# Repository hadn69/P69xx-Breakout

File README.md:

A breakout for Tektronixs P69xx cables, designed for P6960 cables but should work with the others.

It **should** work right now but i would like to make the layout a bit cleaner and get the first small batch made.

### Previous version renders complete with spelling mistakes!

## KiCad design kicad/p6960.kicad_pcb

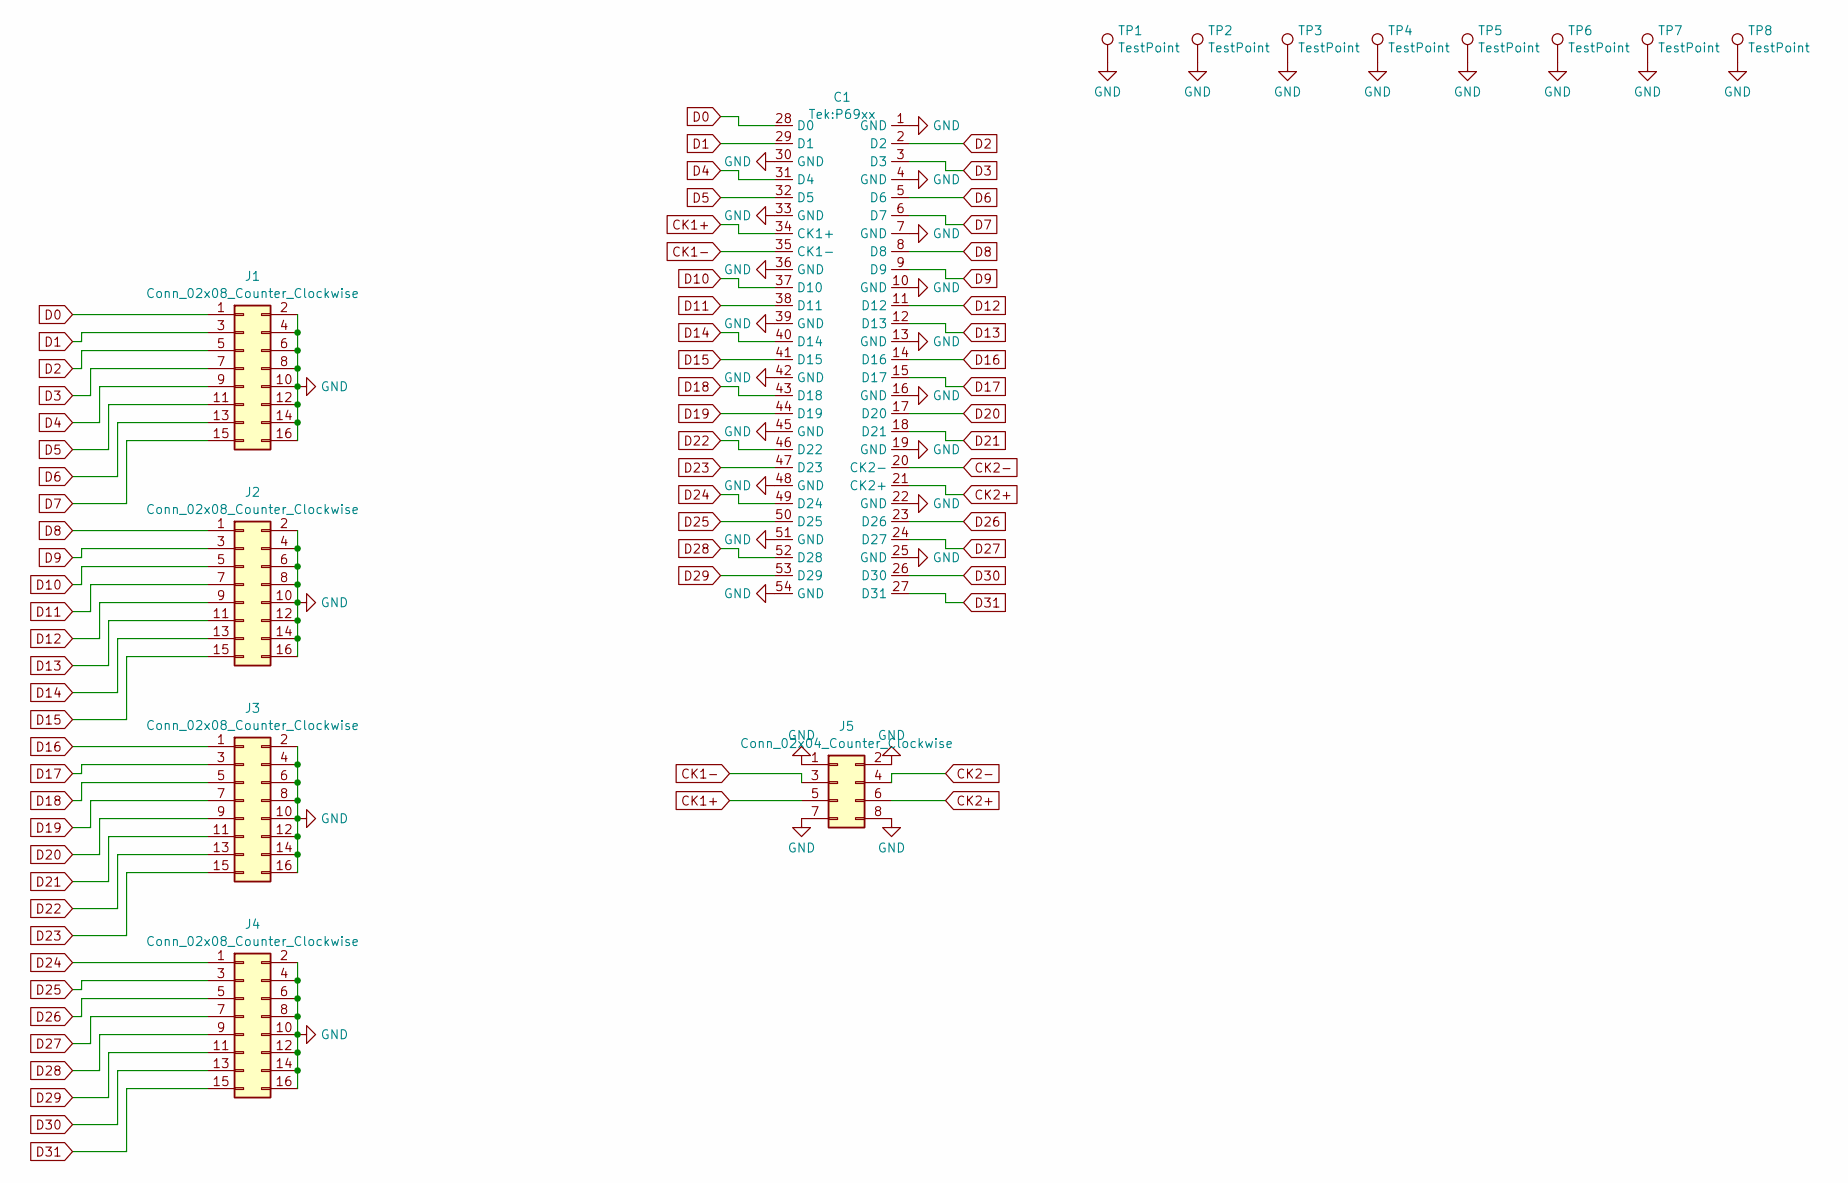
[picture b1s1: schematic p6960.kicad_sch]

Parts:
C1: P69xx
J1, J2, J3, J4: Conn_02x08_Counter_Clockwise; PinHeader_2x08_P2.54mm_Vertical
J5: Conn_02x04_Counter_Clockwise; PinHeader_2x04_P2.54mm_Horizontal
TP1, TP2, TP3, TP4, TP5, TP6, TP7, TP8: TestPoint; TestPoint_Pad_2.0x2.0mm

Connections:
CK1+: C1.34 (CK1+), J5.5
CK1-: C1.35 (CK1-), J5.3
CK2+: C1.21 (CK2+), J5.6
CK2-: C1.20 (CK2-), J5.4
D0: C1.28 (D0), J1.1
D1: C1.29 (D1), J1.3
D2: C1.2 (D2), J1.5
D3: C1.3 (D3), J1.7
D4: C1.31 (D4), J1.9
D5: C1.32 (D5), J1.11
D6: C1.5 (D6), J1.13
D7: C1.6 (D7), J1.15
D8: C1.8 (D8), J2.1
D9: C1.9 (D9), J2.3
D10: C1.37 (D10), J2.5
D11: C1.38 (D11), J2.7
D12: C1.11 (D12), J2.9
D13: C1.12 (D13), J2.11
D14: C1.40 (D14), J2.13
D15: C1.41 (D15), J2.15
D16: C1.14 (D16), J3.1
D17: C1.15 (D17), J3.3
D18: C1.43 (D18), J3.5
D19: C1.44 (D19), J3.7
D20: C1.17 (D20), J3.9
D21: C1.18 (D21), J3.11
D22: C1.46 (D22), J3.13
D23: C1.47 (D23), J3.15
D24: C1.49 (D24), J4.1
D25: C1.50 (D25), J4.3
D26: C1.23 (D26), J4.5
D27: C1.24 (D27), J4.7
D28: C1.52 (D28), J4.9
D29: C1.53 (D29), J4.11
D30: C1.26 (D30), J4.13
D31: C1.27 (D31), J4.15
GND: C1.1 (GND), C1.4 (GND), C1.7 (GND), C1.10 (GND), C1.13 (GND), C1.16 (GND), C1.19 (GND), C1.22 (GND), C1.25 (GND), C1.30 (GND), C1.33 (GND), C1.36 (GND), C1.39 (GND), C1.42 (GND), C1.45 (GND), C1.48 (GND), C1.51 (GND), C1.54 (GND), J1.2, J1.4, J1.6, J1.8, J1.10, J1.12, J1.14, J1.16, J2.2, J2.4, J2.6, J2.8, J2.10, J2.12, J2.14, J2.16, J3.2, J3.4, J3.6, J3.8, J3.10, J3.12, J3.14, J3.16, J4.2, J4.4, J4.6, J4.8, J4.10, J4.12, J4.14, J4.16, J5.1, J5.2, J5.7, J5.8, TP1.1, TP2.1, TP3.1, TP4.1, TP5.1, TP6.1, TP7.1, TP8.1

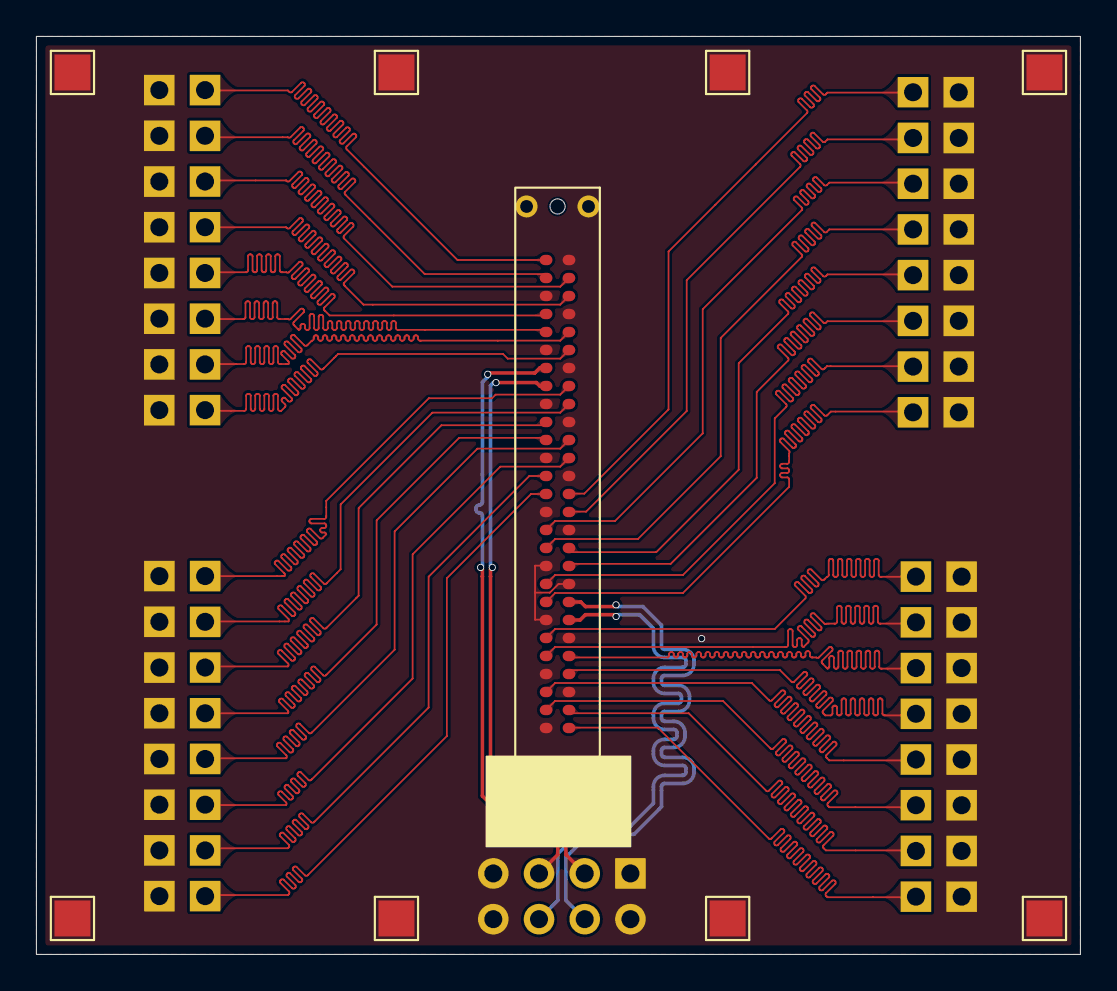
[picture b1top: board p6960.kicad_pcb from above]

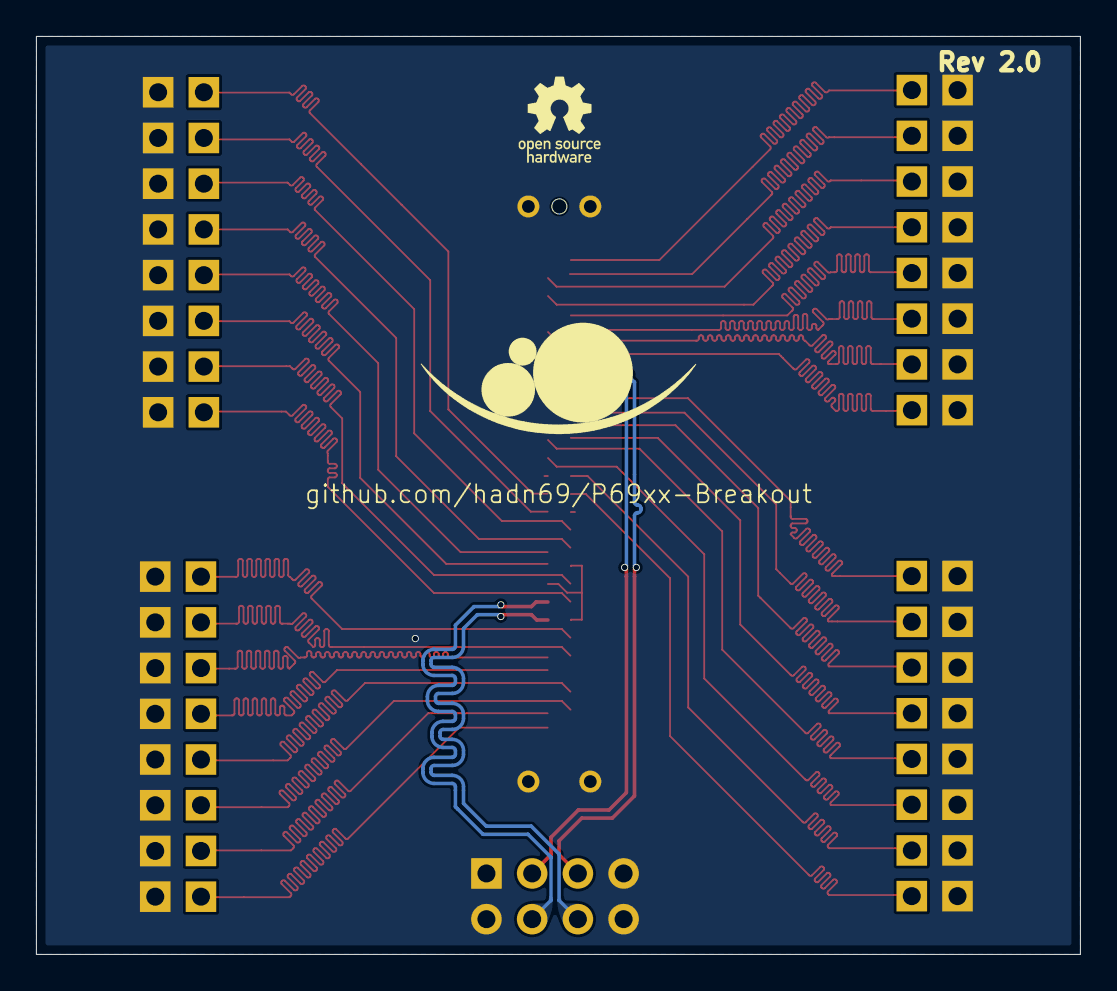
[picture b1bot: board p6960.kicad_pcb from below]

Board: 2 copper layers, 58.0 x 51.0 mm, 14 parts (2 on the bottom side), 37 nets.

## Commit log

2024-09-04 Initial Work
2024-09-06 Design probably works ™️
2024-09-06 done for realz?
2024-09-06 added renders + followed keepout better
2024-09-06 fix spelling
2024-09-06 fix my mild dyslexia
2024-09-07 tuned trace lengths
2024-09-07 centered text
2024-09-07 fixed some shite
2024-11-12 Version 2.0
    Changed header spacing, added real design rules (it fails), tuned all trace lengths to be 38mm, flood fill ground plane, added probe holder model, and more!
